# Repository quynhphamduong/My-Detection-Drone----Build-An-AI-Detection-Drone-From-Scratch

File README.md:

### Commit Convention
- fix : fix a bug
- feat : add new feature
- refactor : refactor code (change the logic)
- wip : add something in progress, may be not working yet
- chore : commit that not add new feature, fix bug or change the logic

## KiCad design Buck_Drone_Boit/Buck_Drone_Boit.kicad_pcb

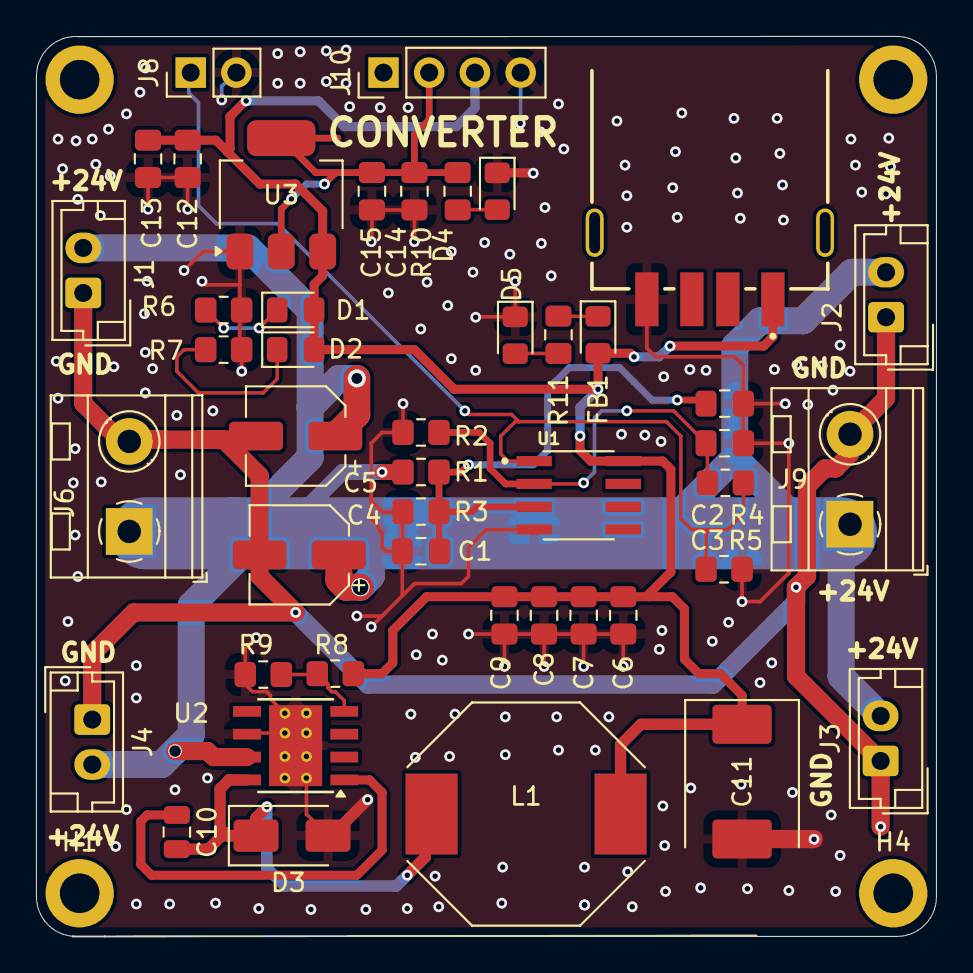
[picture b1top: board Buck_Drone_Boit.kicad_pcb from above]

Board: 2 copper layers, 50.0 x 50.0 mm, 49 parts (0 on the bottom side), 16 nets.

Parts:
C1, C3: 0.1uF; C_0805_2012Metric_Pad1.18x1.45mm_HandSolder
C2, C12, C13, C14, C15: 1uF; C_0805_2012Metric_Pad1.18x1.45mm_HandSolder
C4, C5: 4.7uF- 5x5.4mm; CP_Elec_5x5.4
C6, C7, C8, C9: 105; C_0805_2012Metric_Pad1.18x1.45mm_HandSolder
C10: 0.01uF; C_0805_2012Metric
C11: 220uF; CP_EIA-7361-38_AVX-V_Pad2.18x3.30mm_HandSolder
D1, D2, D4, D5: LED; LED_0805_2012Metric_Pad1.15x1.40mm_HandSolder
D3: SS34; D_SMA
FB1: FerriteBead; LED_0805_2012Metric_Pad1.15x1.40mm_HandSolder
H1, H2, H3, H4: MountingHole; MountingHole_2.2mm_M2_ISO14580_Pad
J1, J2, J3, J4: B2B-XH-A__LF__SN_; JST_EH_B2B-EH-A_1x02_P2.50mm_Vertical
J5, J6: XT60PW-M; TerminalBlock_MetzConnect_Type094_RT03502HBLU_1x02_P5.00mm_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
J8: Conn_01x02_Pin; PinHeader_1x02_P2.54mm_Vertical
J9: USB1046-GF-0190-L-B-A_REVB4; TypeA_Kicad
J10: PinHeader_1x04_P2.54mm_Vertical
L1: 22uH; L_Neosid_SMs95_SMs95p
R1, R2: 100k; R_0805_2012Metric_Pad1.20x1.40mm_HandSolder
R3, R4, R5, R6, R7, R8: 10k; R_0805_2012Metric_Pad1.20x1.40mm_HandSolder
R9: 3.24k; R_0805_2012Metric_Pad1.20x1.40mm_HandSolder
R10: 1k; C_0805_2012Metric_Pad1.18x1.45mm_HandSolder
R11: 5k1; C_0805_2012Metric_Pad1.18x1.45mm_HandSolder
U1: LM358; SOIC127P600X175-8N
U2: TPS5430DDA; TI_SO-PowerPAD-8_ThermalVias
U3: AMS1117-3.3; SOT-223-3_TabPin2

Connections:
3V3: C14.1, C15.1, J10.2, R10.1, U3.2 (VO)
5V: C6.1, C7.1, C8.1, C9.1, C11.1, C12.1, C13.1, D1.2 (A), D2.2 (A), FB1.2, J9.1 (VCC), J10.3, L1.2, R8.1, U1.8 (V+), U3.3 (VI)
24V: C4.1, C5.1, J1.2, J2.2, J3.2, J4.2, J5.1 (+), J6.1 (+), R1.2, U2.7 (VIN)
/PA0: J8.1, R4.1, R5.1, U1.1
GND: C1.1, C2.2, C3.2, C6.2, C7.2, C8.2, C9.2, C11.2, C12.2, C13.2, C14.2, C15.2, D3.2 (A), D4.1 (K), D5.1 (K), J8.2, J9.4 (GND), J10.4, R2.2, R3.1, R5.2, R6.2, R7.2, R9.2, U1.4 (V-), U2.6 (GND), U2.9 (GNDPAD), U3.1 (GND)
GND_IN: C4.2, C5.2, J1.1, J2.1, J3.1, J4.1, J5.2 (-), J6.2 (-)
unnamed: D1.1 (K), R6.1
unnamed: D2.1 (K), R7.1
unnamed: C10.2, D3.1 (K), L1.1, U2.8 (PH)
unnamed: D4.2 (A), R10.2
unnamed: D5.2 (A), R11.1
unnamed: FB1.1, R11.2
unnamed: C1.2, C2.1, R1.1, R3.2, U1.3 (+)
unnamed: C3.1, R2.1, R4.2, U1.2 (-)
unnamed: C10.1, U2.1 (BOOT)
unnamed: R8.2, R9.1, U2.4 (VSENSE)

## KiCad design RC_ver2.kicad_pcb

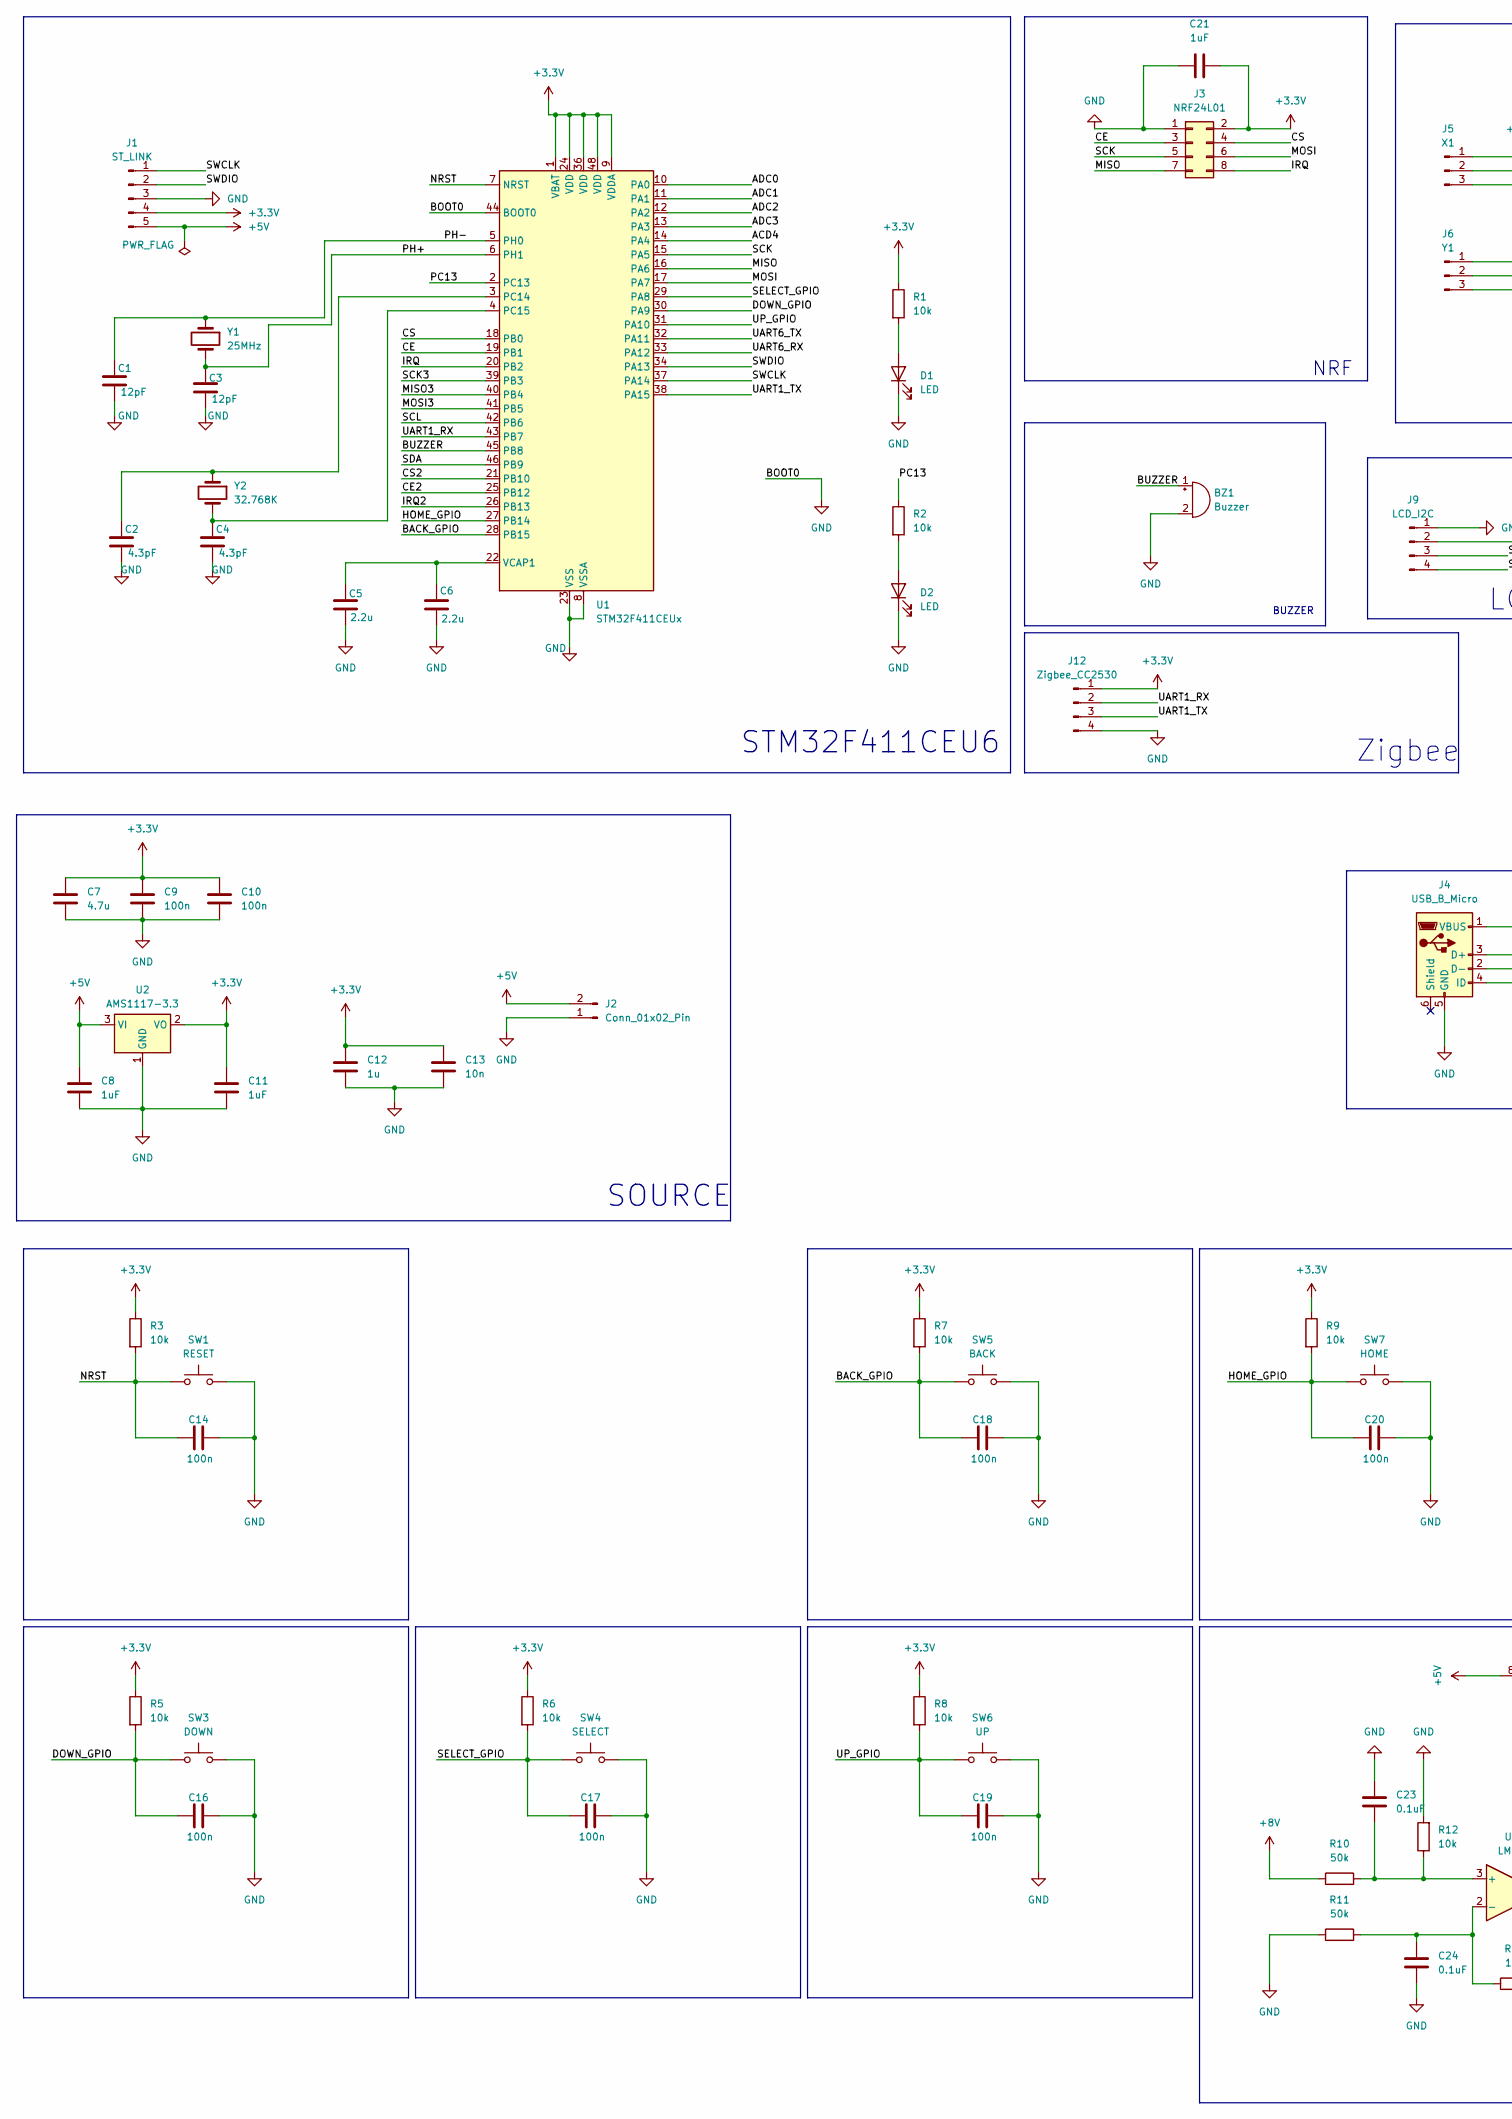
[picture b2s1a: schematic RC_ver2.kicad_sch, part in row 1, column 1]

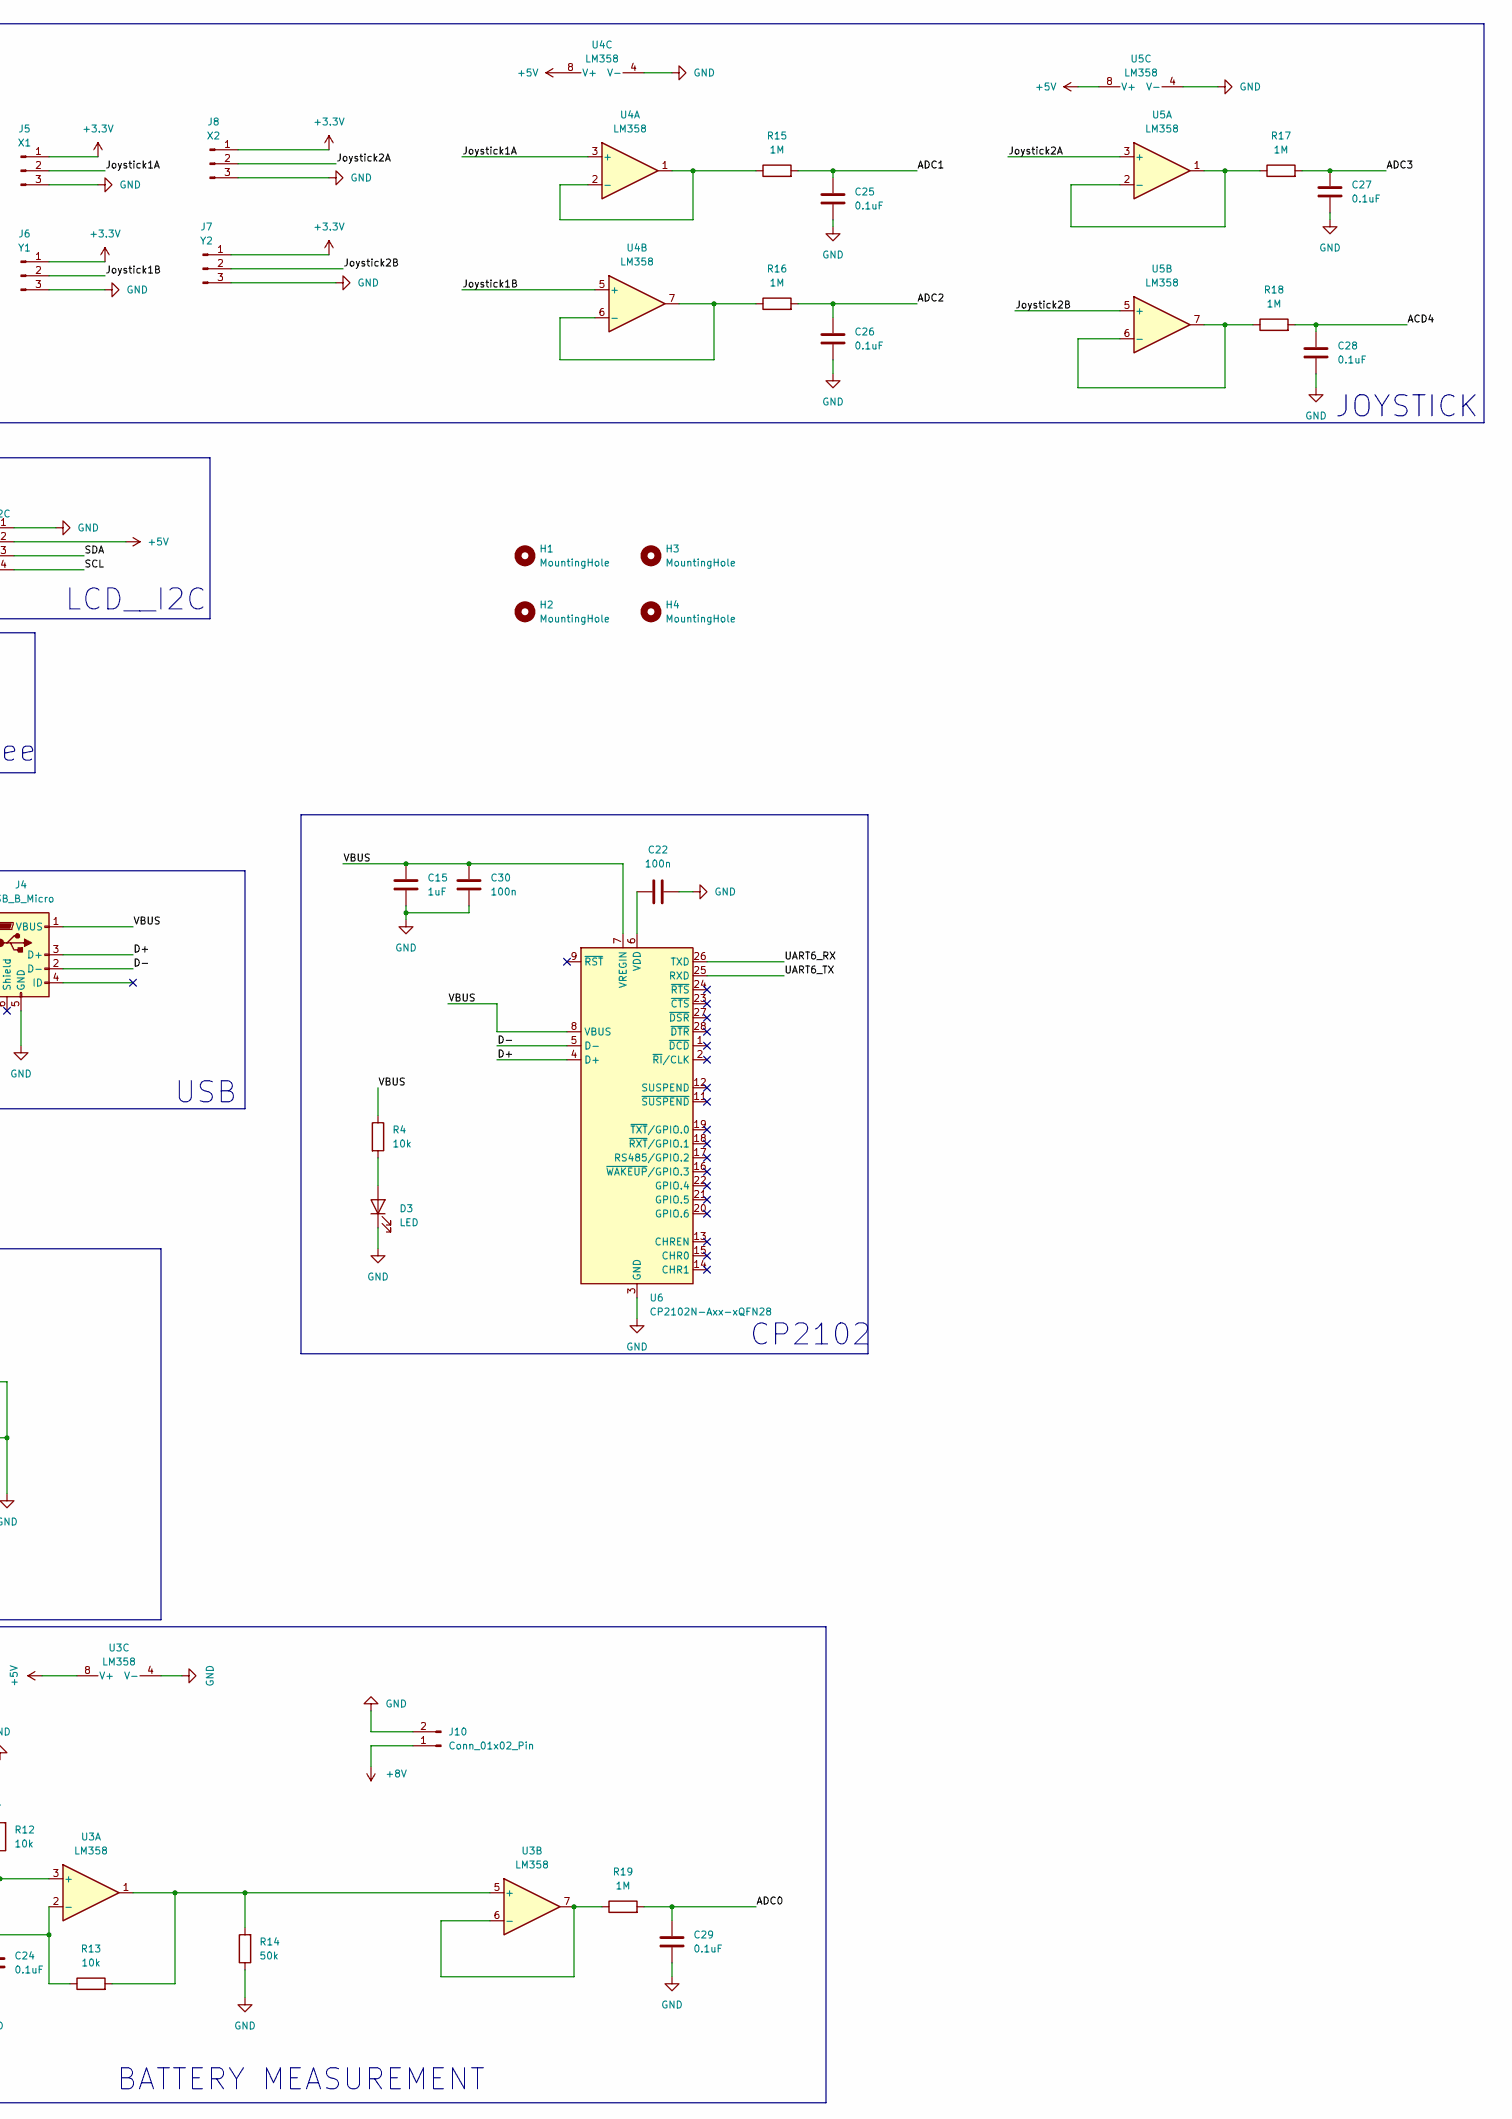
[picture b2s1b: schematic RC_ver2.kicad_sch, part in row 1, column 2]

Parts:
BZ1: Buzzer; Buzzer_12x9.5RM7.6
C1, C3: 12pF; C_0603_1608Metric_Pad1.08x0.95mm_HandSolder
C2: 4.3pF; C_0603_1608Metric
C4: 4.3pF; C_0603_1608Metric_Pad1.08x0.95mm_HandSolder
C5, C6: 2.2u; C_0805_2012Metric_Pad1.18x1.45mm_HandSolder
C7: 4.7u; C_0805_2012Metric_Pad1.18x1.45mm_HandSolder
C8, C11, C15, C21: 1uF; C_0805_2012Metric_Pad1.18x1.45mm_HandSolder
C9, C10, C14, C16, C17, C18, C19, C20, C22, C30: 100n; C_0805_2012Metric_Pad1.18x1.45mm_HandSolder
C12: 1u; C_0805_2012Metric_Pad1.18x1.45mm_HandSolder
C13: 10n; C_0805_2012Metric_Pad1.18x1.45mm_HandSolder
C23, C24, C25, C26, C27, C28, C29: 0.1uF; C_0805_2012Metric_Pad1.18x1.45mm_HandSolder
D1, D2, D3: LED; D_0603_1608Metric_Pad1.05x0.95mm_HandSolder
H1, H2, H3, H4: MountingHole; MountingHole_3.2mm_M3_DIN965_Pad
J1: ST_LINK; PinHeader_1x05_P2.54mm_Vertical
J2, J10: Conn_01x02_Pin; TerminalBlock_Phoenix_MKDS-1,5-2-5.08_1x02_P5.08mm_Horizont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
J3: NRF24L01; PinHeader_2x04_P2.54mm_Vertical
J4: USB_B_Micro; USB_Micro-B_Amphenol_10118194-0001LF_Horizontal
J5: X1; PinHeader_1x03_P2.54mm_Vertical
J6: Y1; PinHeader_1x03_P2.54mm_Vertical
J7: Y2; PinHeader_1x03_P2.54mm_Vertical
J8: X2; PinHeader_1x03_P2.54mm_Vertical
J9: LCD_I2C; PinHeader_1x04_P2.54mm_Vertical
J12: Zigbee_CC2530; PinHeader_1x04_P2.54mm_Vertical
R1, R2, R3, R4, R5, R6, R7, R8, R9, R12, R13: 10k; R_0805_2012Metric_Pad1.20x1.40mm_HandSolder
R10, R11, R14: 50k; R_0805_2012Metric_Pad1.20x1.40mm_HandSolder
R15, R16, R17, R18, R19: 1M; R_0805_2012Metric_Pad1.20x1.40mm_HandSolder
SW1: RESET; SW_SPST_PTS645
SW3: DOWN; SW_SPST_PTS645
SW4: SELECT; SW_SPST_PTS645
SW5: BACK; SW_SPST_PTS645
SW6: UP; SW_SPST_PTS645
SW7: HOME; SW_SPST_PTS645
U1: STM32F411CEUx; QFN-48-1EP_7x7mm_P0.5mm_EP5.6x5.6mm
U2: AMS1117-3.3; SOT-223-3_TabPin2
U3, U4, U5: LM358; SOP-8_3.76x4.96mm_P1.27mm
U6: CP2102N-Axx-xQFN28; QFN-28-1EP_5x5mm_P0.5mm_EP3.35x3.35mm
Y1: 25MHz; Crystal_SMD_5032-2Pin_5.0x3.2mm
Y2: 32.768K; Crystal_AT310_D3.0mm_L10.0mm_Vertical

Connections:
+3.3V: C7.1, C9.1, C10.1, C11.2, C12.1, C13.1, C21.1, J1.4, J3.2, J5.1, J6.1, J7.1, J8.1, J12.1, R1.1, R3.1, R5.1, R6.1, R7.1, R8.1, R9.1, U1.1 (VBAT), U1.9 (VDDA), U1.24 (VDD), U1.36 (VDD), U1.48 (VDD), U2.2 (VO)
+5V: C8.2, J1.5, J2.2, J9.2, U2.3 (VI), U3.8 (V+), U4.8 (V+), U5.8 (V+)
+8V: J10.1, R10.1
/ACD4: C28.1, R18.2, U1.14 (PA4)
/ADC0: C29.1, R19.2, U1.10 (PA0)
/ADC1: C25.1, R15.2, U1.11 (PA1)
/ADC2: C26.1, R16.2, U1.12 (PA2)
/ADC3: C27.1, R17.2, U1.13 (PA3)
/BACK_GPIO: C18.1, R7.2, SW5.1, U1.28 (PB15)
/BUZZER: BZ1.1 (+), U1.45 (PB8)
/CE: J3.3, U1.19 (PB1)
/CE2: U1.25 (PB12)
/CS: J3.4, U1.18 (PB0)
/CS2: U1.21 (PB10)
/D+: J4.3 (D+), U6.4 (D+)
/D-: J4.2 (D-), U6.5 (D-)
/DOWN_GPIO: C16.1, R5.2, SW3.1, U1.30 (PA9)
/HOME_GPIO: C20.1, R9.2, SW7.1, U1.27 (PB14)
/IRQ: J3.8, U1.20 (PB2)
/IRQ2: U1.26 (PB13)
/Joystick1A: J5.2, U4.3 (+)
/Joystick1B: J6.2, U4.5 (+)
/Joystick2A: J8.2, U5.3 (+)
/Joystick2B: J7.2, U5.5 (+)
/MISO: J3.7, U1.16 (PA6)
/MISO3: U1.40 (PB4)
/MOSI: J3.6, U1.17 (PA7)
/MOSI3: U1.41 (PB5)
/NRST: C14.1, R3.2, SW1.1, U1.7 (NRST)
/PC13: R2.1, U1.2 (PC13)
/PH+: C3.1, U1.6 (PH1), Y1.2
/PH-: C1.1, U1.5 (PH0), Y1.1
/SCK: J3.5, U1.15 (PA5)
/SCK3: U1.39 (PB3)
/SCL: J9.4, U1.42 (PB6)
/SDA: J9.3, U1.46 (PB9)
/SELECT_GPIO: C17.1, R6.2, SW4.1, U1.29 (PA8)
/SWCLK: J1.1, U1.37 (PA14)
/SWDIO: J1.2, U1.34 (PA13)
/UART1_RX: J12.2, U1.43 (PB7)
/UART1_TX: J12.3, U1.38 (PA15)
/UART6_RX: U1.33 (PA12), U6.26 (TXD)
/UART6_TX: U1.32 (PA11), U6.25 (RXD)
/UP_GPIO: C19.1, R8.2, SW6.1, U1.31 (PA10)
/VBUS: C15.2, C30.1, J4.1 (VBUS), R4.1, U6.7 (VREGIN), U6.8 (VBUS)
GND: BZ1.2 (-), C1.2, C2.2, C3.2, C4.2, C5.2, C6.2, C7.2, C8.1, C9.2, C10.2, C11.1, C12.2, C13.2, C14.2, C15.1, C16.2, C17.2, C18.2, C19.2, C20.2, C21.2, C22.2, C23.1, C24.2, C25.2, C26.2, C27.2, C28.2, C29.2, C30.2, D1.1 (K), D2.1 (K), D3.1 (K), J1.3, J2.1, J3.1, J4.5 (GND), J5.3, J6.3, J7.3, J8.3, J9.1, J10.2, J12.4, R11.1, R12.2, R14.1, SW1.2, SW3.2, SW4.2, SW5.2, SW6.2, SW7.2, U1.8 (VSSA), U1.23 (VSS), U1.35 (VSS), U1.44 (BOOT0), U1.47 (VSS), U1.49 (VSS), U2.1 (GND), U3.4 (V-), U4.4 (V-), U5.4 (V-), U6.3 (GND), U6.29 (GND)
unnamed: D1.2 (A), R1.2
unnamed: D2.2 (A), R2.2
unnamed: D3.2 (A), R4.2
unnamed: C2.1, U1.3 (PC14), Y2.1
unnamed: C4.1, U1.4 (PC15), Y2.2
unnamed: C5.1, C6.1, U1.22 (VCAP1)
unnamed: C23.2, R10.2, R12.1, U3.3 (+)
unnamed: C24.1, R11.2, R13.1, U3.2 (-)
unnamed: R13.2, R14.2, U3.1, U3.5 (+)
unnamed: R19.1, U3.6 (-), U3.7
unnamed: R15.1, U4.1, U4.2 (-)
unnamed: R16.1, U4.6 (-), U4.7
unnamed: R17.1, U5.1, U5.2 (-)
unnamed: R18.1, U5.6 (-), U5.7
unnamed: C22.1, U6.6 (VDD)

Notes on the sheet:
BUZZER
SOURCE
CP2102
BATTERY MEASUREMENT
LCD__I2C
Zigbee
NRF
JOYSTICK
STM32F411CEU6
USB

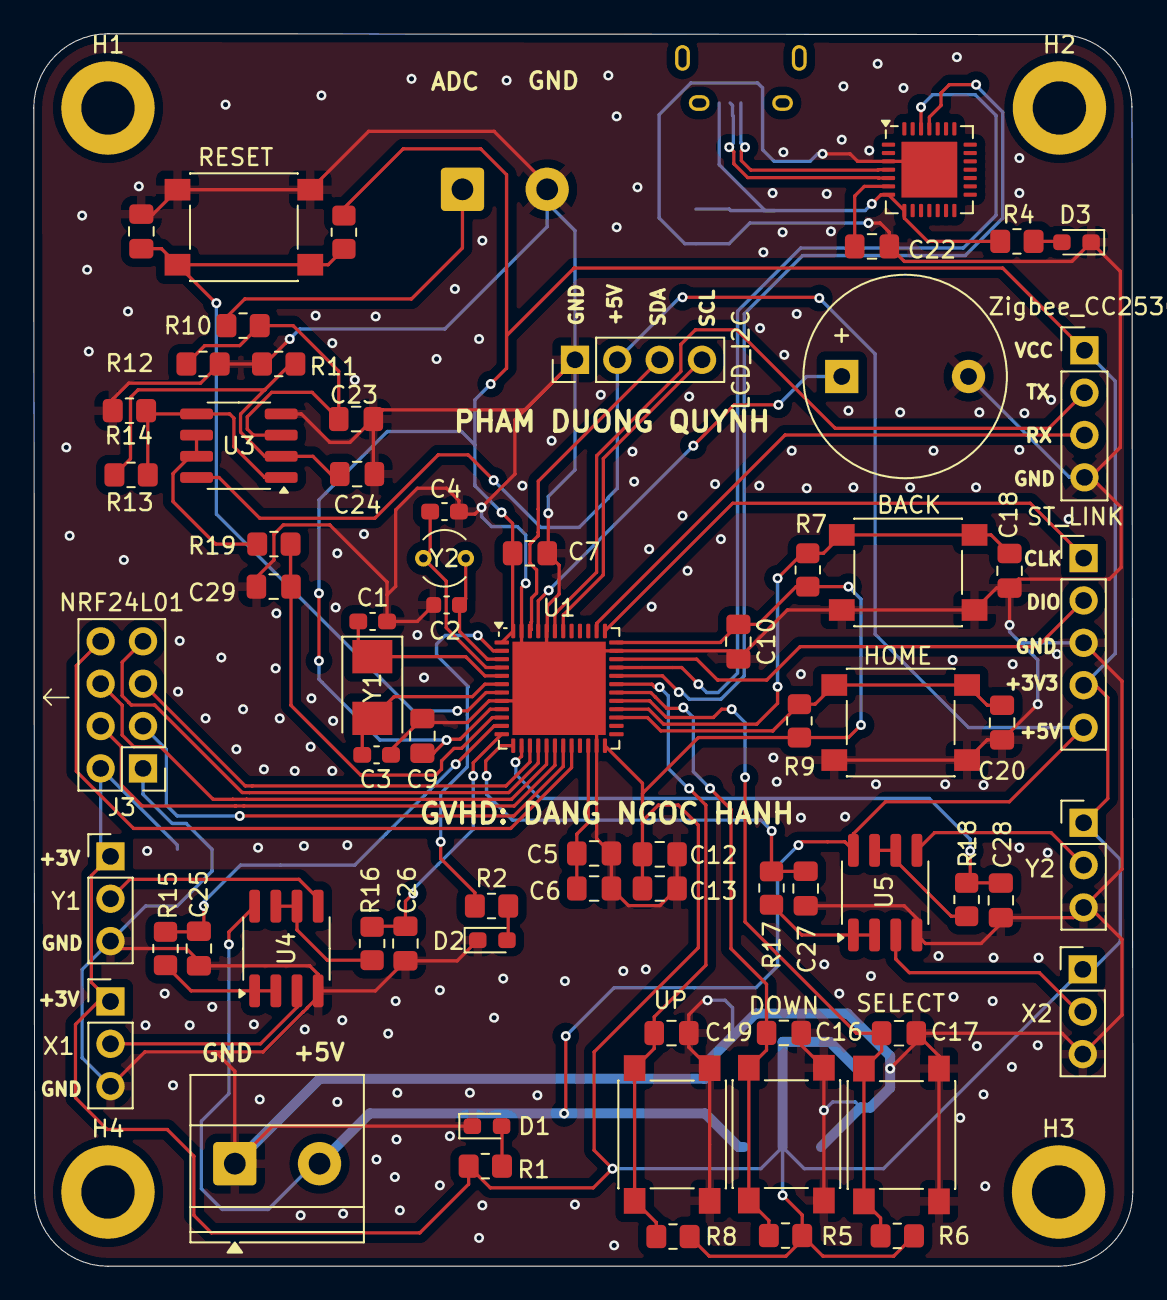
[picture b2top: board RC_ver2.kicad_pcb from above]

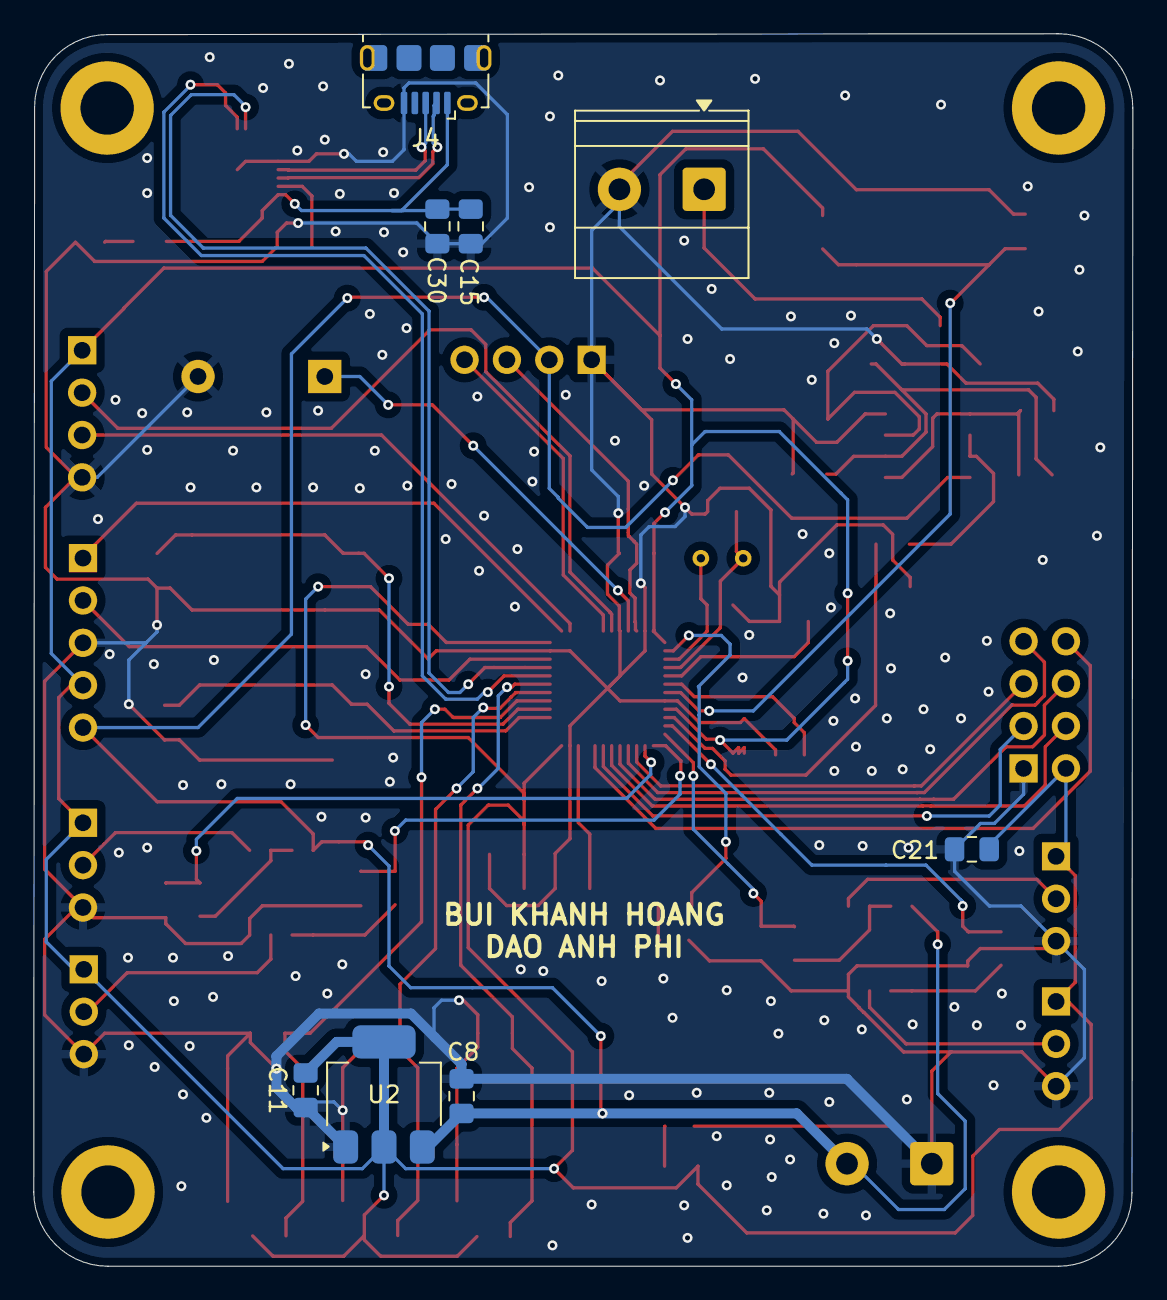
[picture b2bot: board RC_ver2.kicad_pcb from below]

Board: 2 copper layers, 65.9 x 73.9 mm, 82 parts (8 on the bottom side), 55 nets.

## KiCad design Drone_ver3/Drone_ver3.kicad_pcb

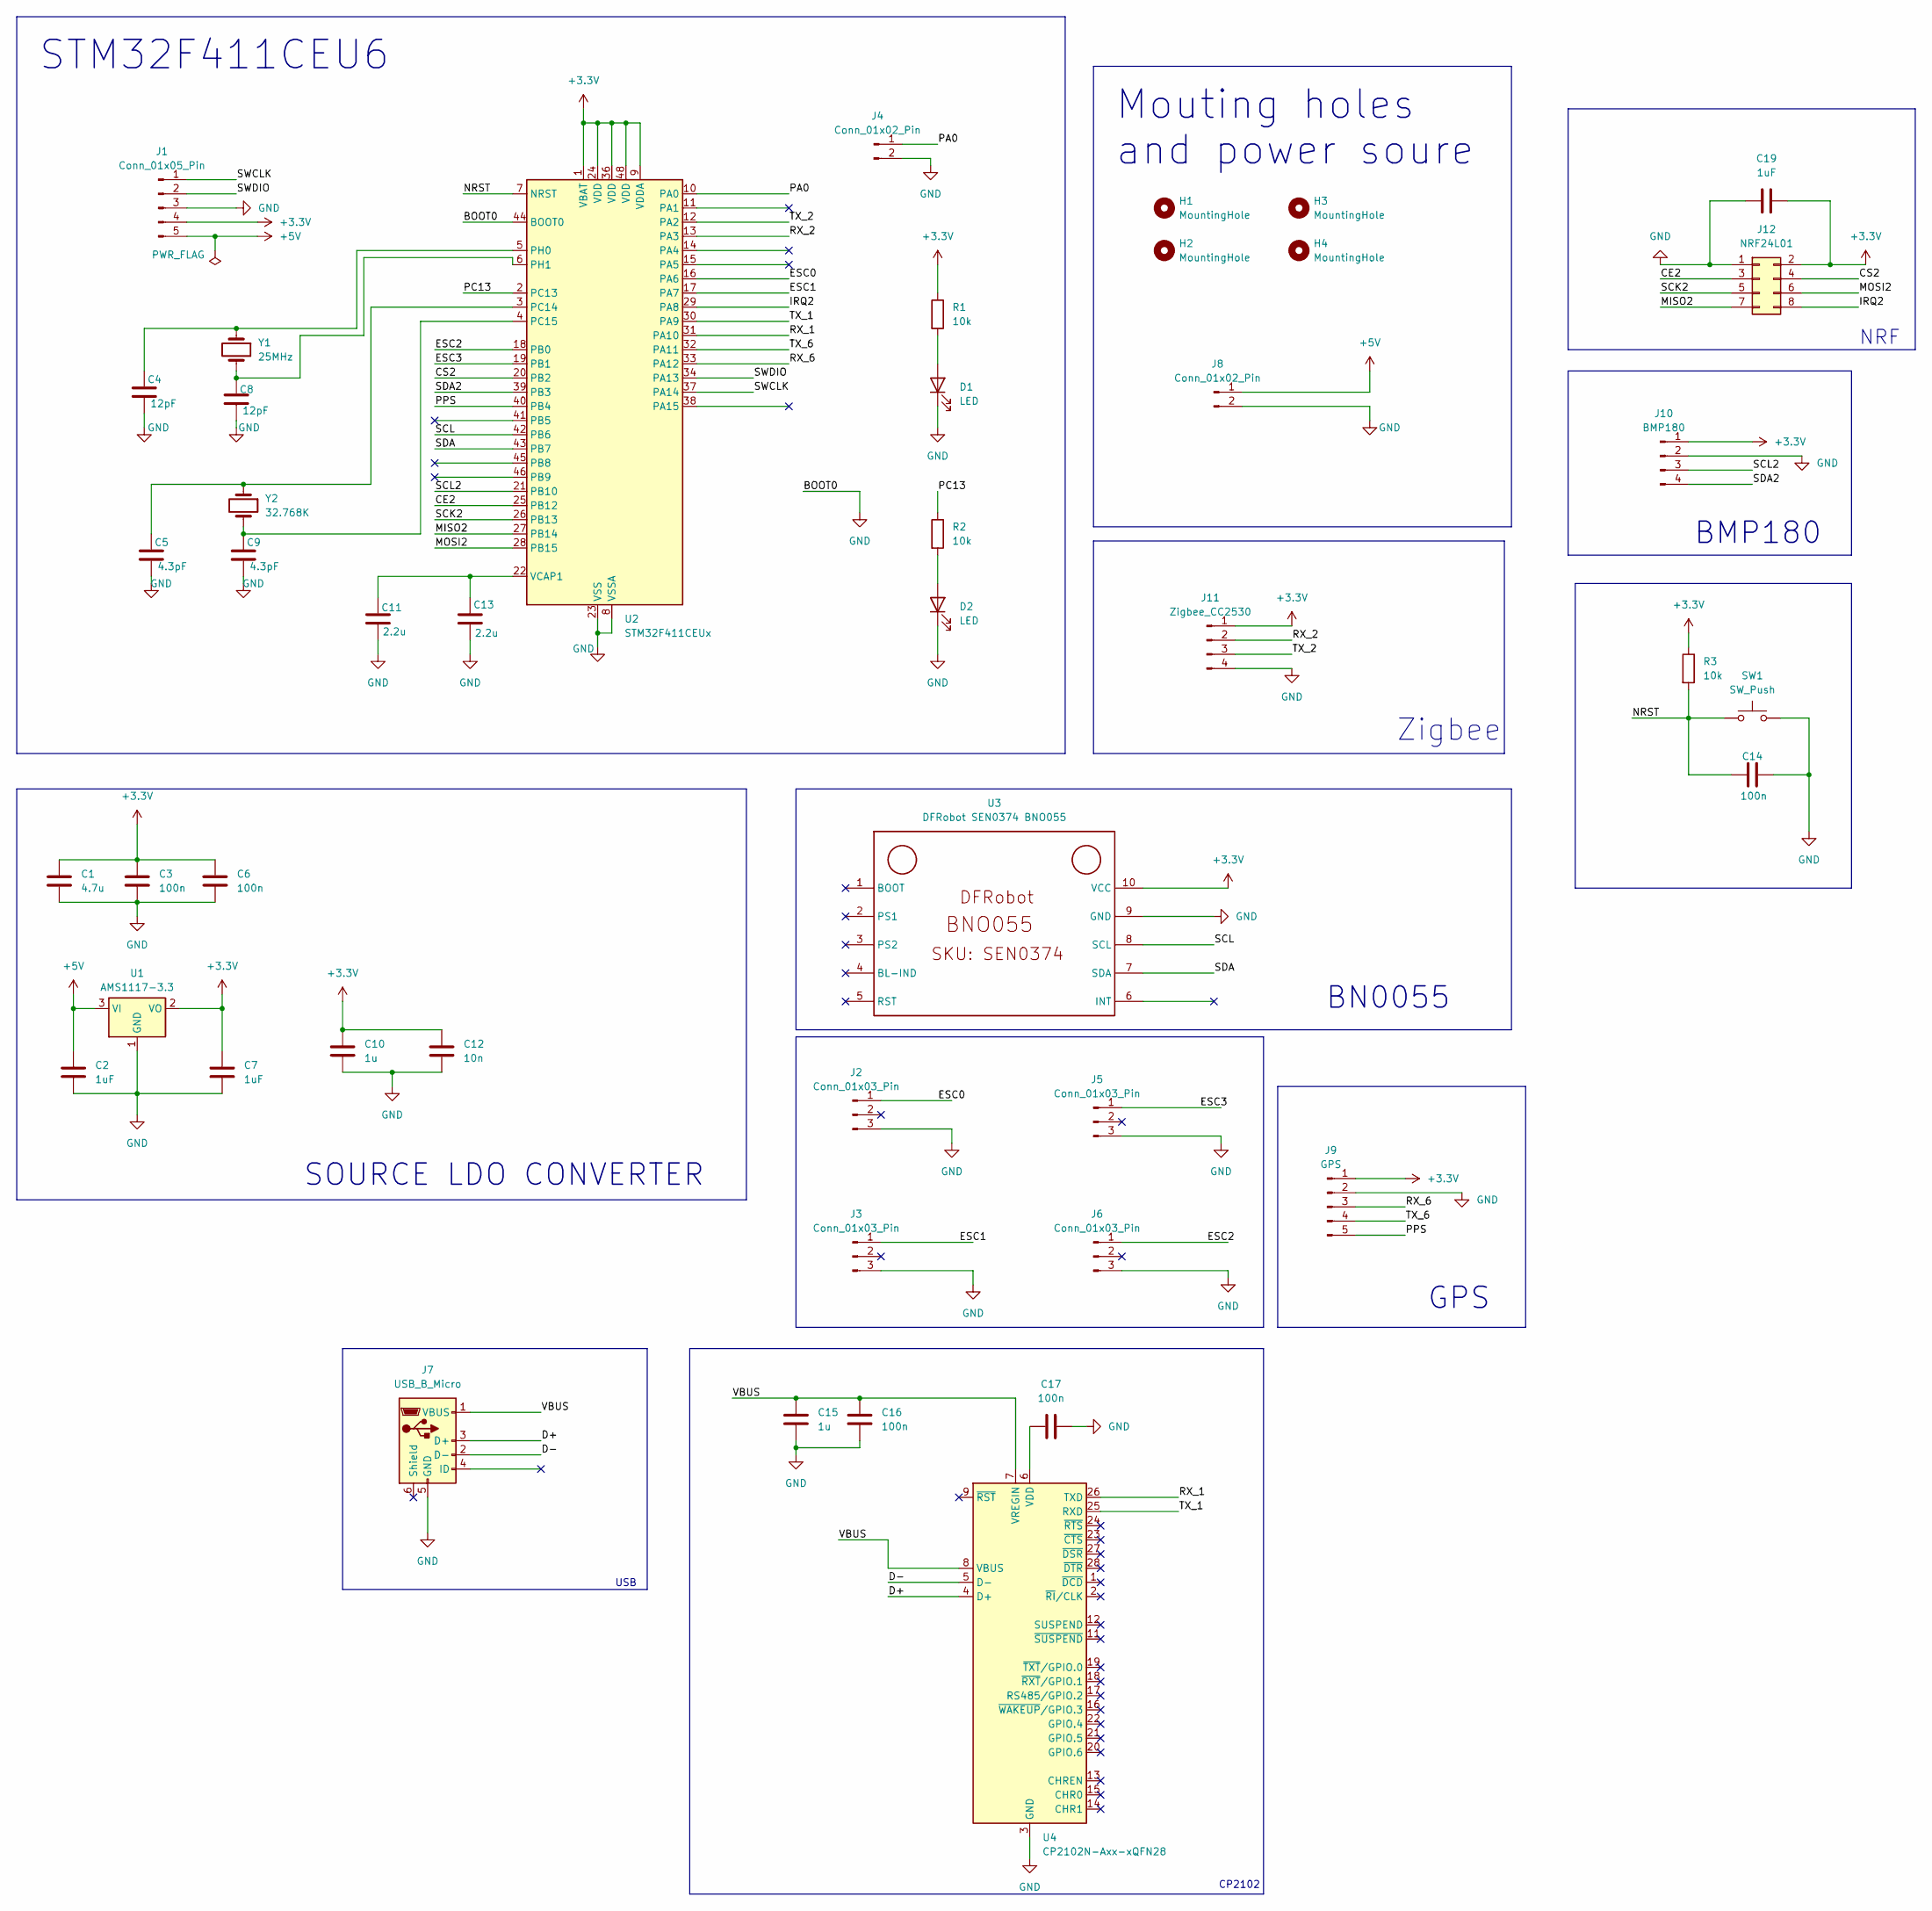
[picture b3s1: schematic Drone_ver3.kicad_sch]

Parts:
C1: 4.7u; C_0805_2012Metric_Pad1.18x1.45mm_HandSolder
C2, C7, C19: 1uF; C_0805_2012Metric_Pad1.18x1.45mm_HandSolder
C3, C6, C14, C16, C17: 100n; C_0805_2012Metric_Pad1.18x1.45mm_HandSolder
C4, C8: 12pF; C_0603_1608Metric_Pad1.08x0.95mm_HandSolder
C5: 4.3pF; C_0603_1608Metric
C9: 4.3pF; C_0603_1608Metric_Pad1.08x0.95mm_HandSolder
C10, C15: 1u; C_0805_2012Metric_Pad1.18x1.45mm_HandSolder
C11, C13: 2.2u; C_0805_2012Metric_Pad1.18x1.45mm_HandSolder
C12: 10n; C_0805_2012Metric_Pad1.18x1.45mm_HandSolder
D1, D2: LED; D_0603_1608Metric_Pad1.05x0.95mm_HandSolder
H1, H2, H3, H4: MountingHole; MountingHole_2.2mm_M2_ISO14580_Pad
J1: Conn_01x05_Pin; PinHeader_1x05_P2.54mm_Vertical
J2, J3, J5, J6: Conn_01x03_Pin; PinHeader_1x03_P2.54mm_Vertical
J4, J8: Conn_01x02_Pin; PinHeader_1x02_P2.54mm_Vertical
J7: USB_B_Micro; USB_Micro-B_Amphenol_10118194-0001LF_Horizontal
J9: GPS; PinHeader_1x05_P2.54mm_Vertical
J10: BMP180; PinHeader_1x04_P2.54mm_Vertical
J11: Zigbee_CC2530; PinHeader_1x04_P2.54mm_Vertical
J12: NRF24L01; PinHeader_2x04_P2.54mm_Vertical
R1, R2: 10k; R_0603_1608Metric_Pad0.98x0.95mm_HandSolder
R3: 10k; R_0805_2012Metric_Pad1.20x1.40mm_HandSolder
SW1: SW_Push; SW_SPST_PTS645
U1: AMS1117-3.3; SOT-223-3_TabPin2
U2: STM32F411CEUx; QFN-48-1EP_7x7mm_P0.5mm_EP5.6x5.6mm
U3: DFRobot SEN0374 BNO055; FOOTPRINT DFROBOT SEN0374 BNO055
U4: CP2102N-Axx-xQFN28; QFN-28-1EP_5x5mm_P0.5mm_EP3.35x3.35mm
Y1: 25MHz; Crystal_SMD_5032-2Pin_5.0x3.2mm
Y2: 32.768K; Crystal_AT310_D3.0mm_L10.0mm_Vertical

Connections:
+3.3V: C1.1, C3.1, C6.1, C7.2, C10.1, C12.1, C19.1, J1.4, J9.1, J10.1, J11.1, J12.2, R1.1, R3.1, U1.2 (VO), U2.1 (VBAT), U2.9 (VDDA), U2.24 (VDD), U2.36 (VDD), U2.48 (VDD), U3.10 (VCC)
+5V: C2.2, J1.5, J8.1, U1.3 (VI)
/CE2: J12.3, U2.25 (PB12)
/CS2: J12.4, U2.20 (PB2)
/D+: J7.3 (D+), U4.4 (D+)
/D-: J7.2 (D-), U4.5 (D-)
/ESC0: J2.1, U2.16 (PA6)
/ESC1: J3.1, U2.17 (PA7)
/ESC2: J6.1, U2.18 (PB0)
/ESC3: J5.1, U2.19 (PB1)
/IRQ2: J12.8, U2.29 (PA8)
/MISO2: J12.7, U2.27 (PB14)
/MOSI2: J12.6, U2.28 (PB15)
/NRST: C14.1, R3.2, SW1.1, U2.7 (NRST)
/PA0: J4.1, U2.10 (PA0)
/PC13: R2.1, U2.2 (PC13)
/PPS: J9.5, U2.40 (PB4)
/RX_1: U2.31 (PA10), U4.26 (TXD)
/RX_2: J11.2, U2.13 (PA3)
/RX_6: J9.3, U2.33 (PA12)
/SCK2: J12.5, U2.26 (PB13)
/SCL: U2.42 (PB6), U3.8 (SCL)
/SCL2: J10.3, U2.21 (PB10)
/SDA: U2.43 (PB7), U3.7 (SDA)
/SDA2: J10.4, U2.39 (PB3)
/SWCLK: J1.1, U2.37 (PA14)
/SWDIO: J1.2, U2.34 (PA13)
/TX_1: U2.30 (PA9), U4.25 (RXD)
/TX_2: J11.3, U2.12 (PA2)
/TX_6: J9.4, U2.32 (PA11)
/VBUS: C15.1, C16.1, J7.1 (VBUS), U4.7 (VREGIN), U4.8 (VBUS)
GND: C1.2, C2.1, C3.2, C4.2, C5.2, C6.2, C7.1, C8.2, C9.2, C10.2, C11.2, C12.2, C13.2, C14.2, C15.2, C16.2, C17.2, C19.2, D1.1 (K), D2.1 (K), J1.3, J2.3, J3.3, J4.2, J5.3, J6.3, J7.5 (GND), J8.2, J9.2, J10.2, J11.4, J12.1, SW1.2, U1.1 (GND), U2.8 (VSSA), U2.23 (VSS), U2.35 (VSS), U2.44 (BOOT0), U2.47 (VSS), U2.49 (VSS), U3.9 (GND), U4.3 (GND), U4.29 (GND)
unnamed: D1.2 (A), R1.2
unnamed: D2.2 (A), R2.2
unnamed: C5.1, U2.3 (PC14), Y2.1
unnamed: C9.1, U2.4 (PC15), Y2.2
unnamed: C4.1, U2.5 (PH0), Y1.1
unnamed: C8.1, U2.6 (PH1), Y1.2
unnamed: C11.1, C13.1, U2.22 (VCAP1)
unnamed: C17.1, U4.6 (VDD)

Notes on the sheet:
CP2102
BMP180
GPS
SOURCE LDO CONVERTER
USB
NRF
Zigbee
BN0055
STM32F411CEU6
Mouting holes and power soure

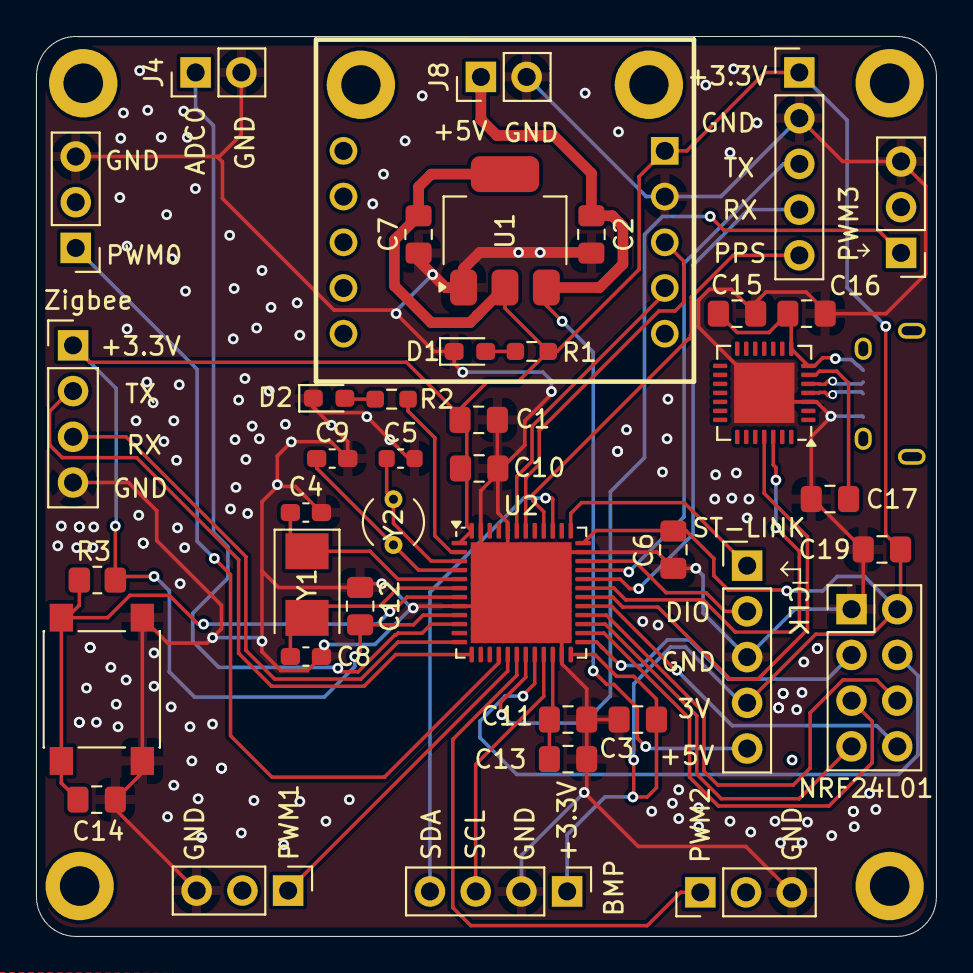
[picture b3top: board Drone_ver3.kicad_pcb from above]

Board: 2 copper layers, 50.0 x 50.0 mm, 46 parts (1 on the bottom side), 40 nets.

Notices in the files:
Core/Src/main.c:
Copyright (c) 2025 STMicroelectronics.
All rights reserved.
This software is licensed under terms that can be found in the LICENSE file
